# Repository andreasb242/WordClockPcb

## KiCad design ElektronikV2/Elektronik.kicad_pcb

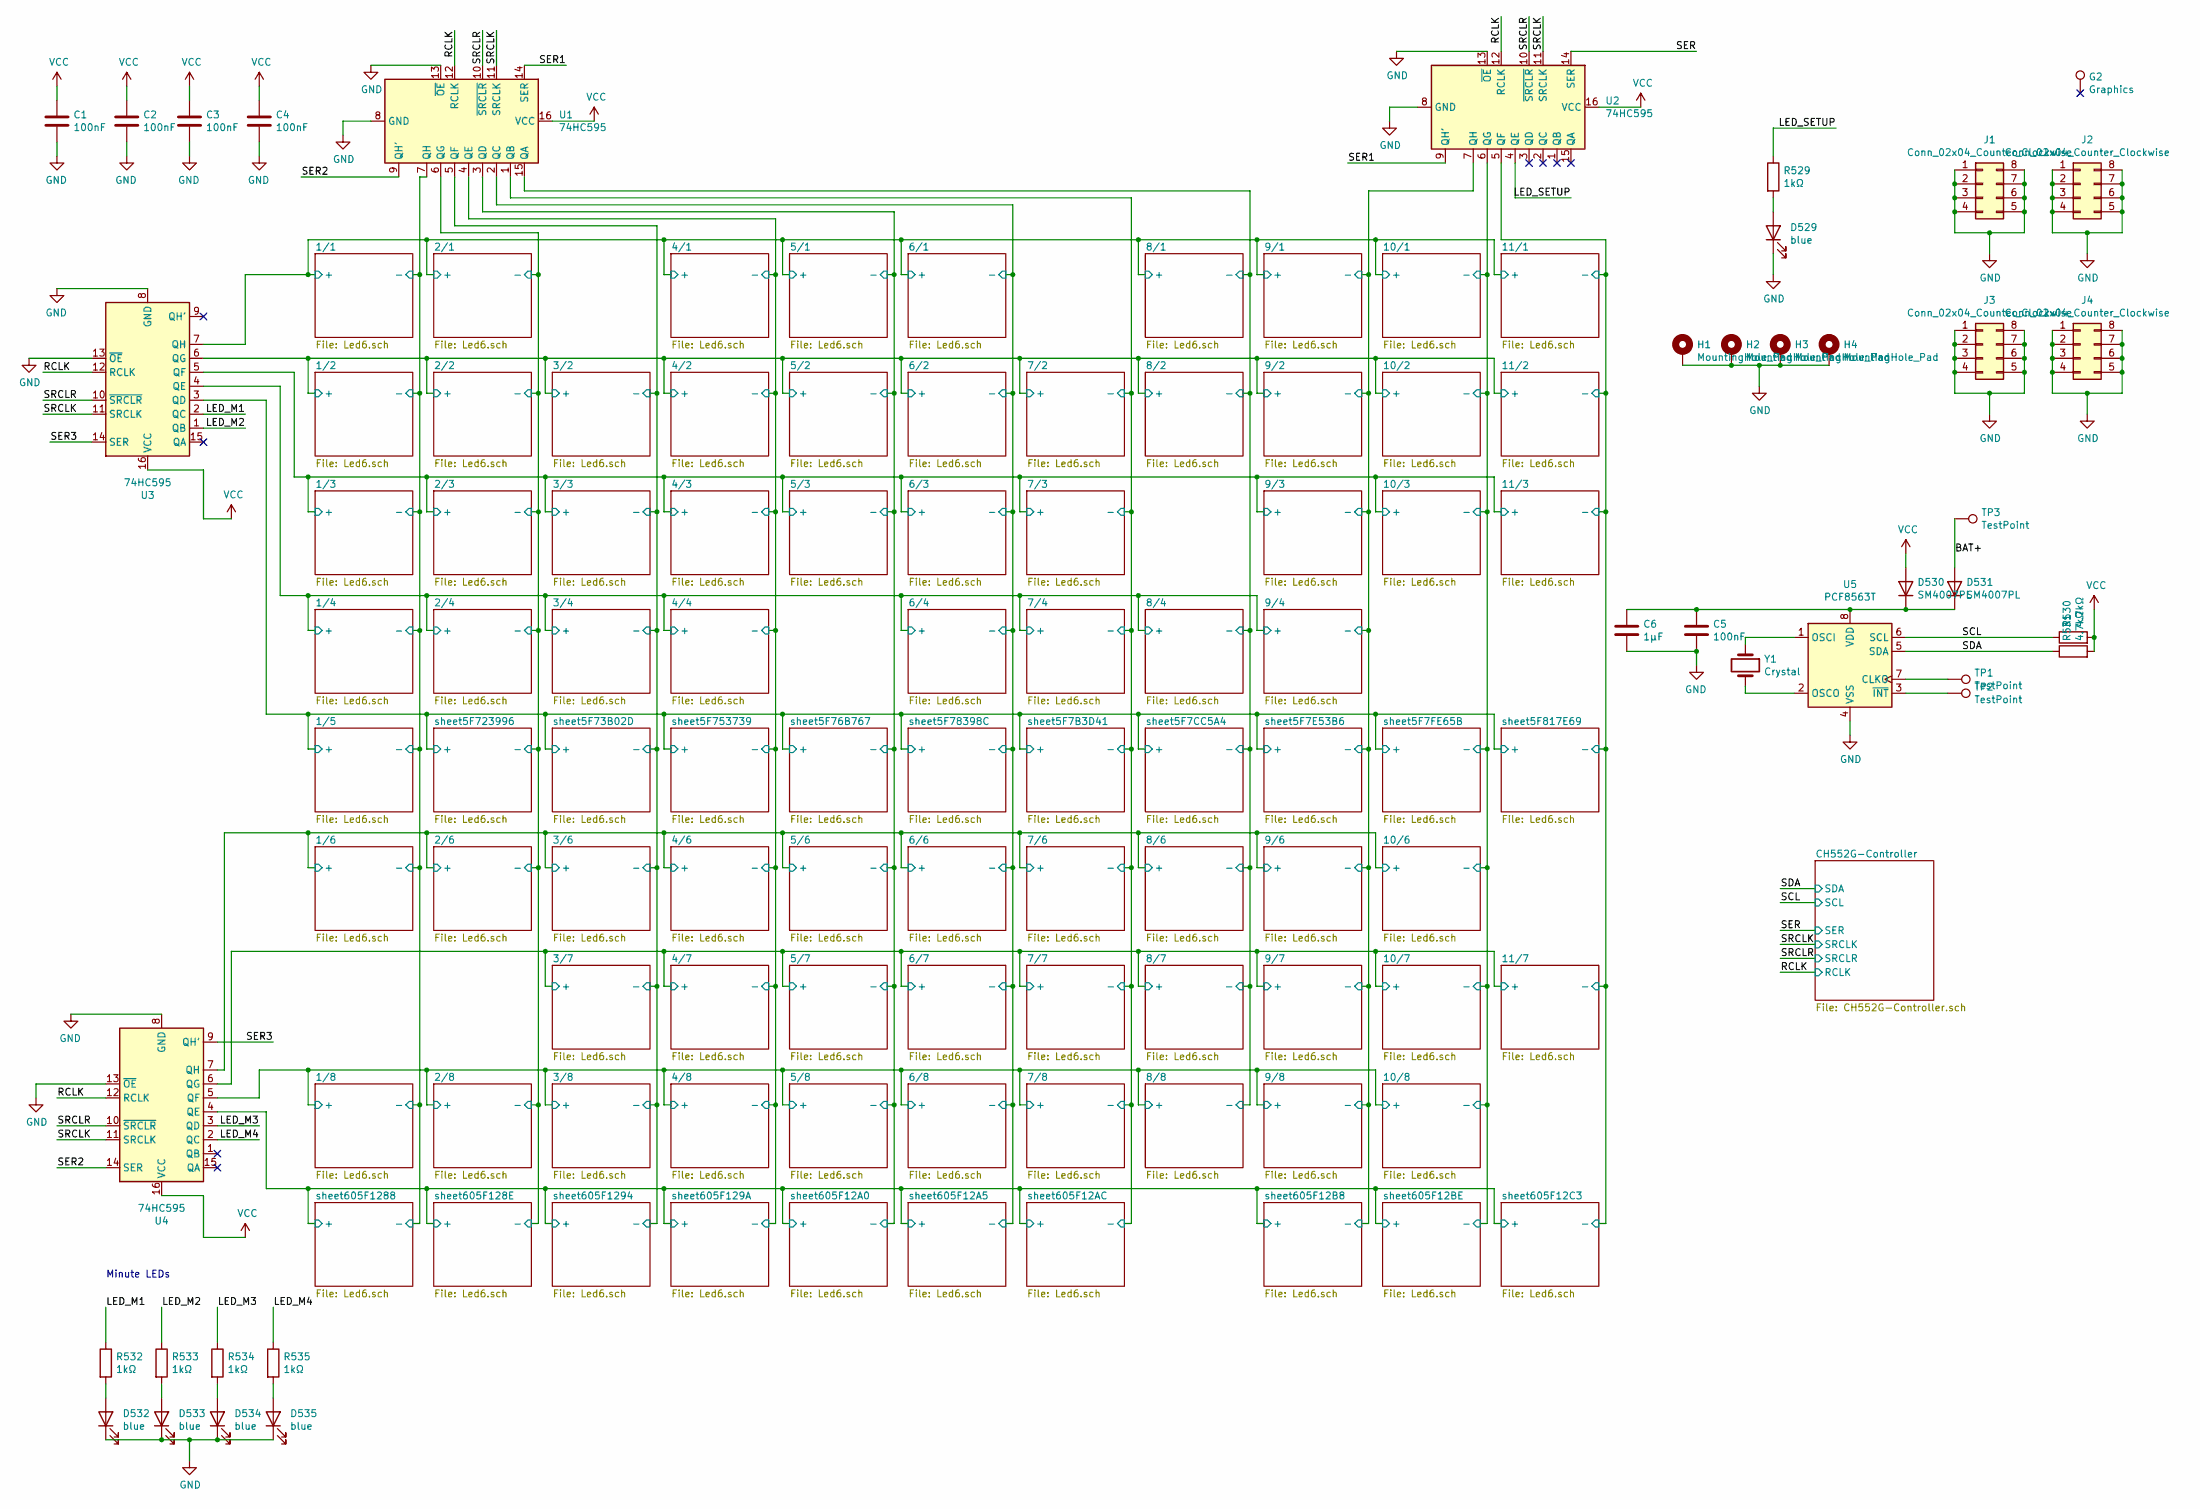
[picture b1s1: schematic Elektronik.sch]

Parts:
C1, C2, C3, C4, C5: 100nF; C_0603_1608Metric
C6: 1µF; C_0603_1608Metric
D529, D532, D533, D534, D535: blue; LED_0805_2012Metric_Pad1.15x1.40mm_HandSolder
D530, D531: SM4007PL; D_SOD-123F
G2: Graphics; sw
H1, H2, H3, H4: MountingHole_Pad; MountingHole_4.3mm_M4_Pad_Via
J1, J2, J3, J4: Conn_02x04_Counter_Clockwise; PinHeader_2x04_P2.54mm_Vertical
R529, R532, R533, R534, R535: 1kΩ; R_0402_1005Metric
R530, R531: 4.7kΩ; R_0402_1005Metric
TP1, TP2, TP3: TestPoint; TestPoint_Pad_1.5x1.5mm
U1, U2, U3, U4: 74HC595; SOIC-16_3.9x9.9mm_P1.27mm
U5: PCF8563T; SOIC-8_3.9x4.9mm_P1.27mm
Y1: Crystal; Crystal_SMD_3215-2Pin_3.2x1.5mm

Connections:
/1/1/+: U3.7 (QH); also elsewhere on the board
/1/1/-: U1.7 (QH); also elsewhere on the board
/1/2/+: U3.6 (QG); also elsewhere on the board
/1/3/+: U3.5 (QF); also elsewhere on the board
/1/4/+: U3.4 (QE); also elsewhere on the board
/1/5/+: U3.3 (QD); also elsewhere on the board
/1/6/+: U4.7 (QH); also elsewhere on the board
/1/8/+: U4.5 (QF); also elsewhere on the board
/2/1/-: U1.6 (QG); also elsewhere on the board
/3/2/-: U1.5 (QF); also elsewhere on the board
/4/1/-: U1.4 (QE); also elsewhere on the board
/5/1/-: U1.3 (QD); also elsewhere on the board
/6/1/-: U1.2 (QC); also elsewhere on the board
/7/2/-: U1.1 (QB); also elsewhere on the board
/8/1/-: U1.15 (QA); also elsewhere on the board
/9/1/-: U2.7 (QH); also elsewhere on the board
/10/1/-: U2.6 (QG); also elsewhere on the board
/10/7/+: U4.6 (QG); also elsewhere on the board
/11/1/-: U2.5 (QF); also elsewhere on the board
/BAT+: D531.2 (A), TP3.1
/LED_M1: R532.1, U3.2 (QC)
/LED_M2: R533.1, U3.1 (QB)
/LED_M3: R534.1, U4.3 (QD)
/LED_M4: R535.1, U4.2 (QC)
/LED_SETUP: R529.1, U2.4 (QE)
/RCLK: U1.12 (RCLK), U2.12 (RCLK), U3.12 (RCLK), U4.12 (RCLK); also elsewhere on the board
/SCL: R530.1, U5.6 (SCL); also elsewhere on the board
/SDA: R531.1, U5.5 (SDA); also elsewhere on the board
/SER: U2.14 (SER); also elsewhere on the board
/SER1: U1.14 (SER), U2.9 (QH')
/SER2: U1.9 (QH'), U4.14 (SER)
/SER3: U3.14 (SER), U4.9 (QH')
/SRCLK: U1.11 (SRCLK), U2.11 (SRCLK), U3.11 (SRCLK), U4.11 (SRCLK); also elsewhere on the board
/SRCLR: U1.10 (~SRCLR), U2.10 (~SRCLR), U3.10 (~SRCLR), U4.10 (~SRCLR); also elsewhere on the board
/sheet605F1288/+: U4.4 (QE); also elsewhere on the board
GND: C1.2, C2.2, C3.2, C4.2, C5.2, C6.2, D529.1 (K), D532.1 (K), D533.1 (K), D534.1 (K), D535.1 (K), H1.1, H2.1, H3.1, H4.1, J1.1, J1.2, J1.3, J1.4, J1.5, J1.6, J1.7, J1.8, J2.1, J2.2, J2.3, J2.4, J2.5, J2.6, J2.7, J2.8, J3.1, J3.2, J3.3, J3.4, J3.5, J3.6, J3.7, J3.8, J4.1, J4.2, J4.3, J4.4, J4.5, J4.6, J4.7, J4.8, U1.8 (GND), U1.13 (~OE), U2.8 (GND), U2.13 (~OE), U3.8 (GND), U3.13 (~OE), U4.8 (GND), U4.13 (~OE), U5.4 (VSS); also elsewhere on the board
unnamed: C5.1, C6.1, D530.1 (K), D531.1 (K), U5.8 (VDD)
unnamed: D529.2 (A), R529.2
unnamed: D532.2 (A), R532.2
unnamed: D533.2 (A), R533.2
unnamed: D534.2 (A), R534.2
unnamed: D535.2 (A), R535.2
unnamed: TP1.1, U5.7 (CLKO)
unnamed: TP2.1, U5.3 (~INT~)
unnamed: U5.1 (OSCI), Y1.1
unnamed: U5.2 (OSCO), Y1.2
VCC: C1.1, C2.1, C3.1, C4.1, D530.2 (A), R530.2, R531.2, U1.16 (VCC), U2.16 (VCC), U3.16 (VCC), U4.16 (VCC); also elsewhere on the board

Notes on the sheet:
Minute LEDs
